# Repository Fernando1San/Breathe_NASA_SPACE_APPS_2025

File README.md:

# Breathe_NASA_SPACE_APPS_2025
2025 Hackathon for NASA all code and information
## Overview
Breathe is a mobile and IoT application developed in MIT App Inventor that enables real time monitoring and prediction of air quality, integrating information from Sentinel-5P TROPOMI satellite mission and low-cost environmental sensors.

The system collects, analyzes, and visualizes air pollution data to provide users with personalized health recommendations based on their environment and personal profile.

In addition to its mobile and IoT components, Breathe also includes an AI powered chatbot linked to ChatGPT, which allows users to interact naturally with the system,  asking questions about air quality, understanding pollutant levels, and receiving guidance on how to stay safe in varying atmospheric conditions.

Furthermore, the project features a dedicated web platform that shares educational resources, real-time updates, and information about the project’s technologies and environmental impact. This website aims to raise public awareness and promote community participation in air-quality monitoring.
The goal of Breathe is to protect public health, raise environmental awareness, and promote citizen participation in air quality measurement—combining satellite science, sensor technology, and artificial intelligence in a collaborative ecosystem.

## App Video 
https://youtube.com/shorts/2b4xFa8w2Ws?feature=share

## Download App
https://drive.google.com/file/d/1CBSrnyRV_KwNRinMbwZoVWh6irQ37grQ/view?usp=drivesdk

## Web Site
https://s0ma9dp.github.io/BREATHE/

## Repo Navigation suggestions
Throughout the folders, you’ll find README files that explain each section and its code.

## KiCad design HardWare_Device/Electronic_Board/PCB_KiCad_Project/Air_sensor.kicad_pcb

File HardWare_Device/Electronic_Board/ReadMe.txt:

#Electronic PCB
La PCB está basada en el microcontrolador ESP32-WROOM-32UE, un módulo con Wi-Fi y Bluetooth integrados, ideal para aplicaciones IoT que requieren comunicación inalámbrica estable y bajo consumo energético.
El circuito permite la conexión y lectura de diversos sensores de gases y partículas, ofreciendo una plataforma compacta y versátil para el monitoreo ambiental.

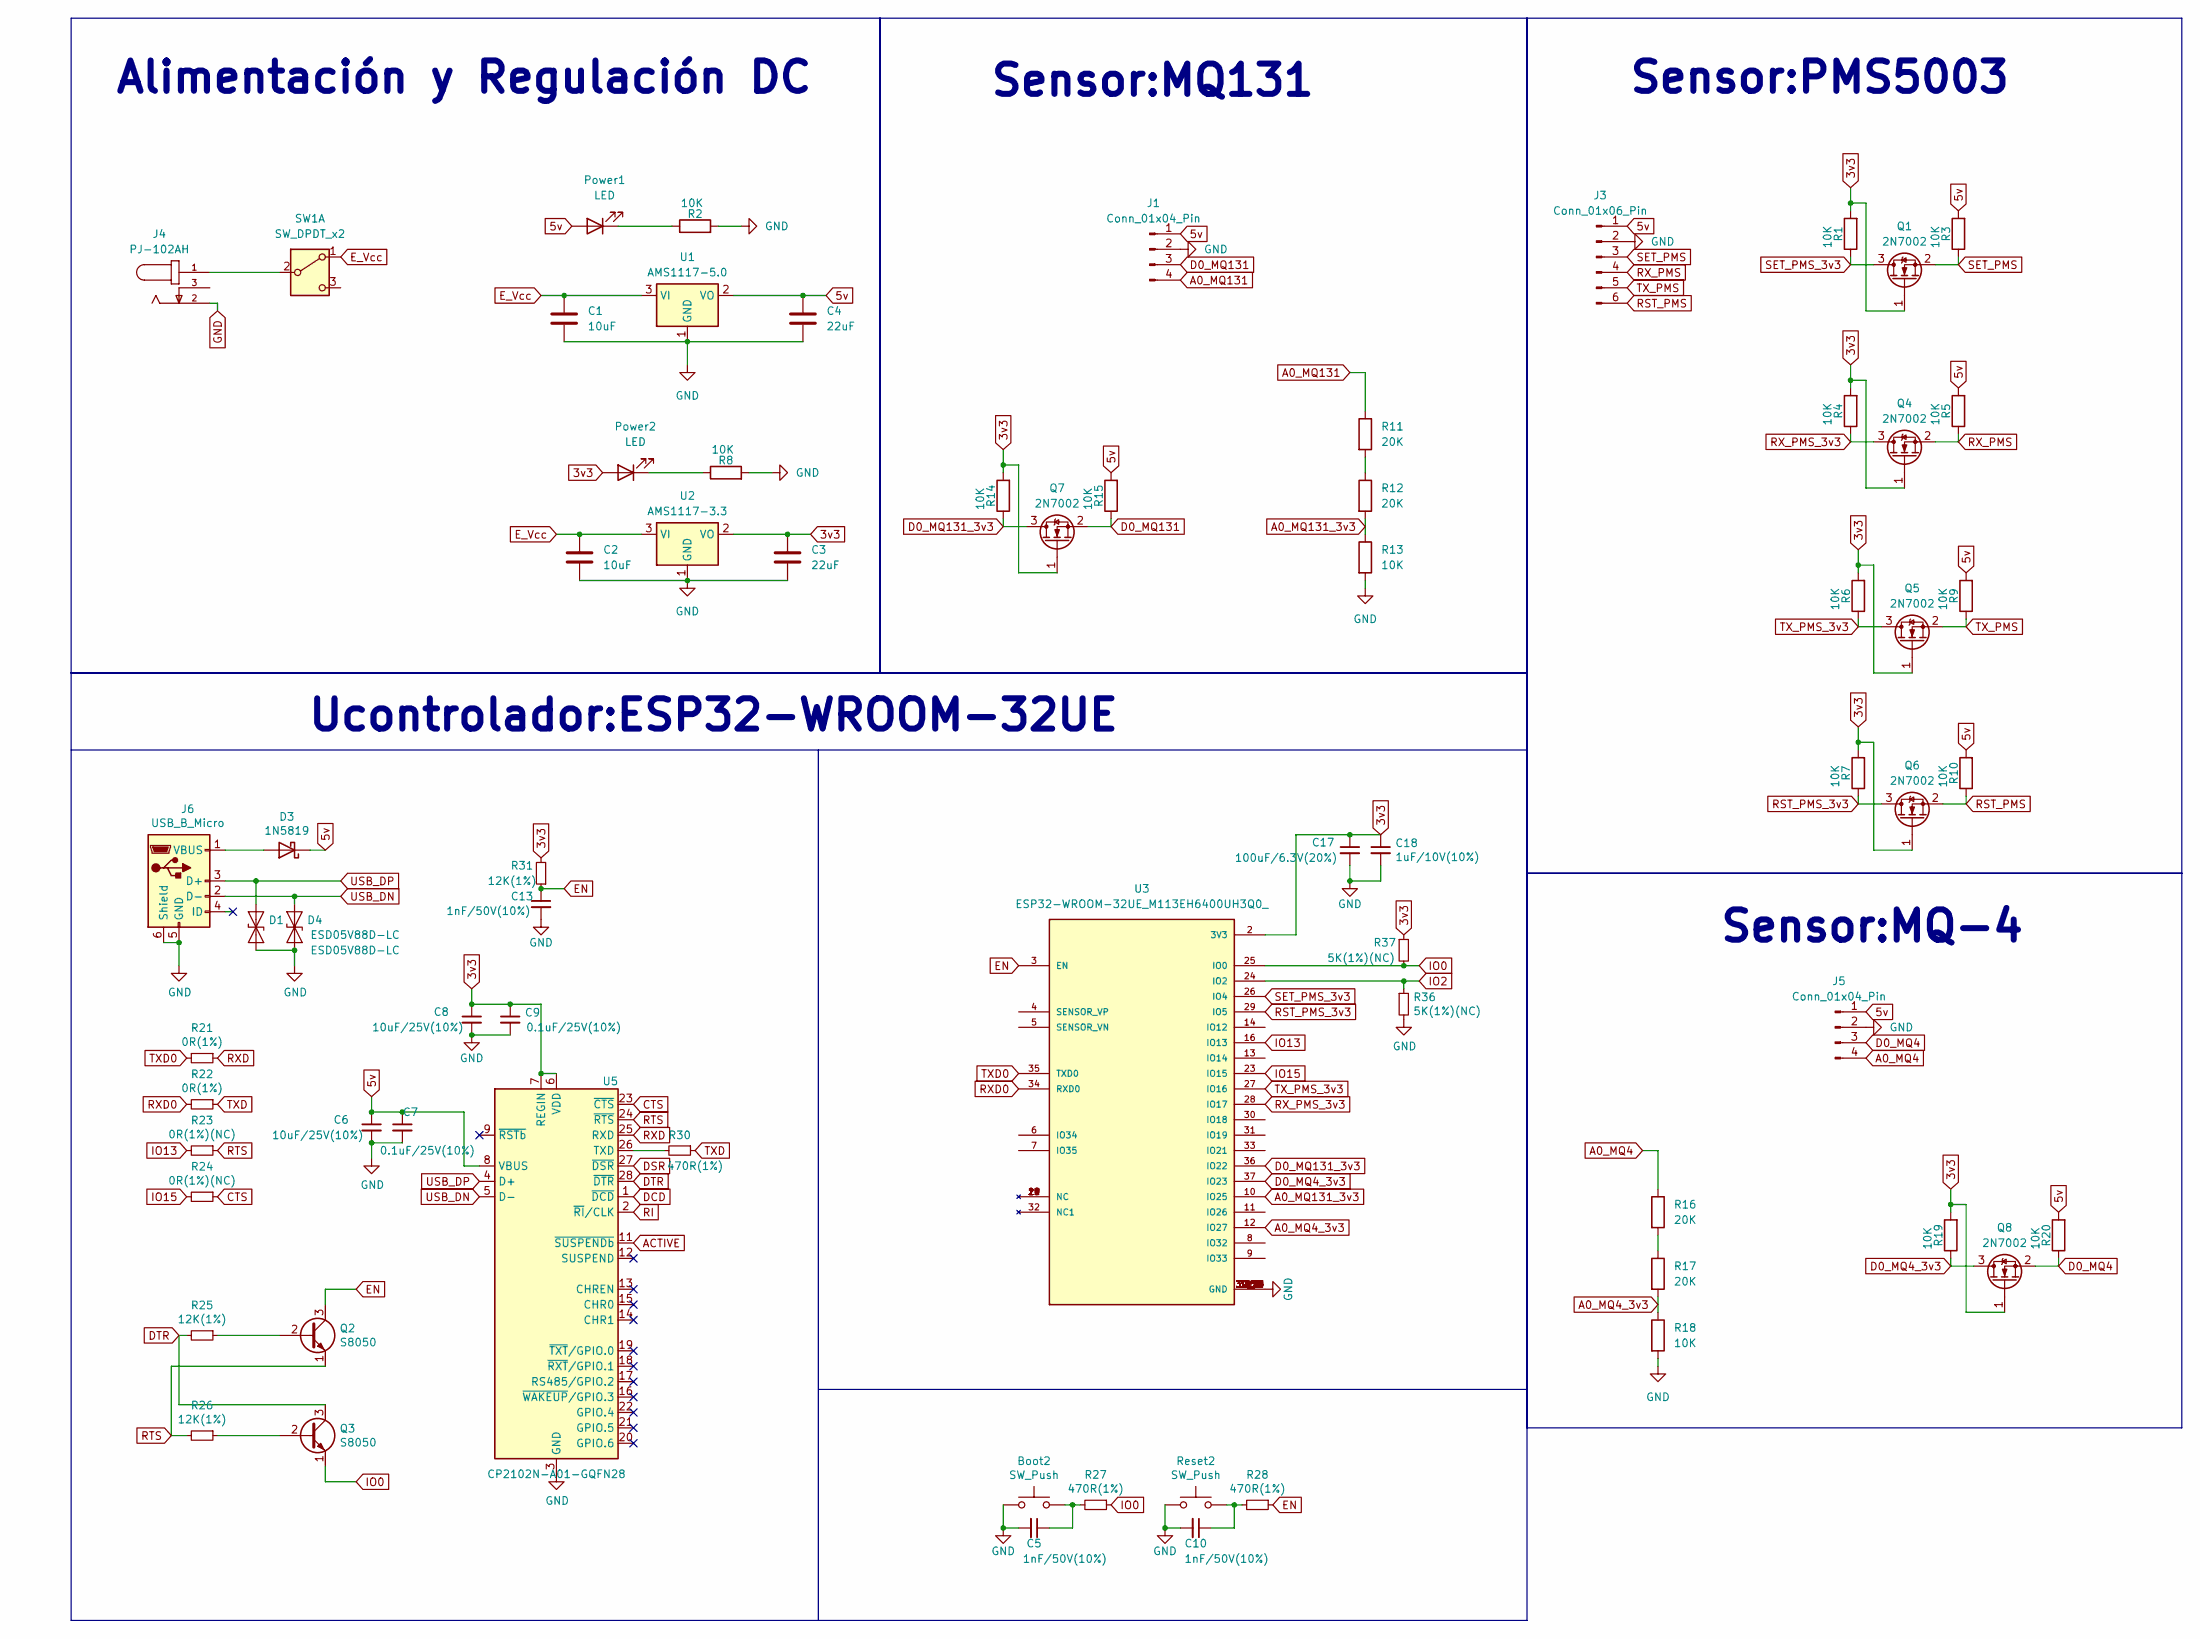
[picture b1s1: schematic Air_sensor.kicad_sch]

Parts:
Boot2: SW_Push; SW_Push_SPST_NO_Alps_SKRK
C1, C2: 10uF; CP_Radial_D4.0mm_P2.00mm
C3, C4: 22uF; CP_Radial_D4.0mm_P2.00mm
C5, C10, C13: 1nF/50V(10%); C_0402_1005Metric
C6, C8: 10uF/25V(10%); C_0603_1608Metric
C7, C9: 0.1uF/25V(10%); C_0402_1005Metric
C17: 100uF/6.3V(20%); C_0603_1608Metric
C18: 1uF/10V(10%); C_0402_1005Metric
D1, D4: ESD05V88D-LC; D_0402_1005Metric
D3: 1N5819; D_0402_1005Metric
J1, J5: Conn_01x04_Pin; PinHeader_1x04_P2.54mm_Horizontal
J3: Conn_01x06_Pin; PinHeader_1x06_P2.54mm_Horizontal
J4: PJ-102AH; CUI_PJ-102AH
J6: USB_B_Micro; USB_Micro-B_Molex_47346-0001
Power1, Power2: LED; LED_1206_3216Metric_Pad1.42x1.75mm_HandSolder
Q1, Q4, Q5, Q6, Q7, Q8: 2N7002; SOT-23
Q2, Q3: S8050; SOT-23
R1, R3, R4, R5, R6, R7, R9, R10, R14, R15, R19, R20: 10K; R_0402_1005Metric
R2, R8, R13, R18: 10K; R_1206_3216Metric_Pad1.30x1.75mm_HandSolder
R11, R12, R16, R17: 20K; R_1206_3216Metric_Pad1.30x1.75mm_HandSolder
R21, R22: 0R(1%); R_0402_1005Metric
R23, R24: 0R(1%)(NC); R_0402_1005Metric
R25, R26, R31: 12K(1%); R_0402_1005Metric
R27, R28: 470R(1%); R_0402_1005Metric
R30: 470R(1%); C_0402_1005Metric
R36, R37: 5K(1%)(NC); R_0402_1005Metric
Reset2: SW_Push; SW_Push_SPST_NO_Alps_SKRK
SW1: SW_DPDT_x2; SW_CK_JS202011AQN_DPDT_Angled
U1: AMS1117-5.0; SOT-223-3_TabPin2
U2: AMS1117-3.3; SOT-223-3_TabPin2
U3: ESP32-WROOM-32UE_M113EH6400UH3Q0_; MODULE_ESP32-WROOM-32UE_M113EH6400UH3Q0_; PARTREV 1.2
U5: CP2102N-A01-GQFN28; QFN-28-1EP_5x5mm_P0.5mm_EP3.35x3.35mm

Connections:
3v3: C3.1, C8.1, C9.1, C17.1, C18.1, Power2.2 (A), Q1.1 (G), Q4.1 (G), Q5.1 (G), Q6.1 (G), Q7.1 (G), Q8.1 (G), R1.2, R4.2, R6.2, R7.2, R14.2, R19.2, R31.2, R37.1, U2.2 (VO), U3.2 (3V3), U5.6 (VDD), U5.7 (REGIN)
5v: C4.1, C6.1, C7.1, D3.1 (K), J1.1, J3.1, J5.1, Power1.2 (A), R3.2, R5.2, R9.2, R10.2, R15.2, R20.2, U1.2 (VO), U5.8 (VBUS)
A0_MQ4: J5.4, R16.1
A0_MQ4_3v3: R17.2, R18.1, U3.12 (IO27)
A0_MQ131: J1.4, R11.1
A0_MQ131_3v3: R12.2, R13.1, U3.10 (IO25)
ACTIVE: U5.11 (~SUSPENDb)
CTS: R24.1, U5.23 (~CTS)
D0_MQ4: J5.3, Q8.2 (S), R20.1
D0_MQ4_3v3: Q8.3 (D), R19.1, U3.37 (IO23)
D0_MQ131: J1.3, Q7.2 (S), R15.1
D0_MQ131_3v3: Q7.3 (D), R14.1, U3.36 (IO22)
DCD: U5.1 (~DCD)
DSR: U5.27 (~DSR)
DTR: Q3.3 (C), R25.2, U5.28 (~DTR)
EN: C13.1, Q2.3 (C), R28.1, R31.1, U3.3 (EN)
E_Vcc: C1.1, C2.1, SW1.1 (A), U1.3 (VI), U2.3 (VI)
GND: Boot2.1, C1.2, C2.2, C3.2, C4.2, C5.2, C6.2, C7.2, C8.2, C9.2, C10.2, C13.2, C17.2, C18.2, D1.2 (A2), D4.2 (A2), J1.2, J3.2, J4.2, J5.2, J6.5 (GND), J6.6 (Shield), R2.2, R8.2, R13.2, R18.2, R36.2, Reset2.1, U1.1 (GND), U2.1 (GND), U3.1 (GND), U3.15 (GND), U3.38 (GND), U3.39_1 (GND), U3.39_2 (GND), U3.39_3 (GND), U3.39_4 (GND), U3.39_5 (GND), U3.39_6 (GND), U3.39_7 (GND), U3.39_8 (GND), U3.39_9 (GND), U3.39_10 (GND), U3.39_11 (GND), U3.39_12 (GND), U3.39_13 (GND), U3.39_14 (GND), U3.39_15 (GND), U3.39_16 (GND), U3.39_17 (GND), U3.39_18 (GND), U3.39_19 (GND), U3.39_20 (GND), U3.39_21 (GND), U5.3 (GND), U5.29 (GND)
IO0: Q3.1 (E), R27.1, R37.2, U3.25 (IO0)
IO2: R36.1, U3.24 (IO2)
IO13: R23.2, U3.16 (IO13)
IO15: R24.2, U3.23 (IO15)
unnamed: Boot2.2, C5.1, R27.2
unnamed: C10.1, R28.2, Reset2.2
unnamed: D3.2 (A), J6.1 (VBUS)
unnamed: Power1.1 (K), R2.1
unnamed: Power2.1 (K), R8.1
unnamed: Q2.2 (B), R25.1
unnamed: Q3.2 (B), R26.1
unnamed: R11.2, R12.1
unnamed: R16.2, R17.1
unnamed: J4.1, SW1.2 (B)
unnamed: R30.2, U5.26 (TXD)
RI: U5.2 (~RI/CLK)
RST_PMS: J3.6, Q6.2 (S), R10.1
RST_PMS_3v3: Q6.3 (D), R7.1, U3.29 (IO5)
RTS: Q2.1 (E), R23.1, R26.2, U5.24 (~RTS)
RXD: R21.1, U5.25 (RXD)
RXD0: R22.2, U3.34 (RXD0)
RX_PMS: J3.4, Q4.2 (S), R5.1
RX_PMS_3v3: Q4.3 (D), R4.1, U3.28 (IO17)
SET_PMS: J3.3, Q1.2 (S), R3.1
SET_PMS_3v3: Q1.3 (D), R1.1, U3.26 (IO4)
TXD: R22.1, R30.1
TXD0: R21.2, U3.35 (TXD0)
TX_PMS: J3.5, Q5.2 (S), R9.1
TX_PMS_3v3: Q5.3 (D), R6.1, U3.27 (IO16)
USB_DN: D4.1 (A1), J6.2 (D-), U5.5 (D-)
USB_DP: D1.1 (A1), J6.3 (D+), U5.4 (D+)

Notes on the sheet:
Sensor:MQ-4
Sensor:MQ131
Ucontrolador:ESP32-WROOM-32UE
Sensor:PMS5003
Alimentación y Regulación DC

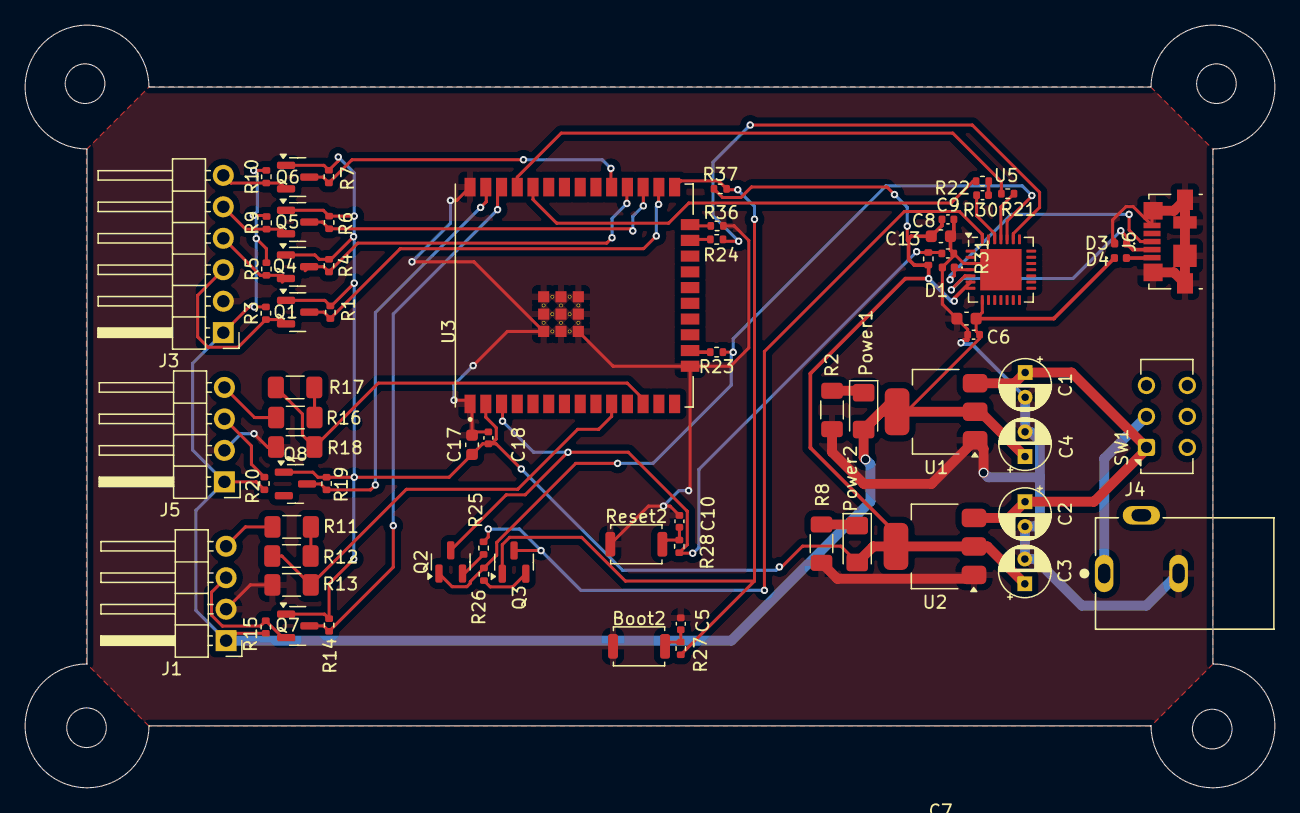
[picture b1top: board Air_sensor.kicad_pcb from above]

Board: 2 copper layers, 100.9 x 61.6 mm, 70 parts (0 on the bottom side), 45 nets.

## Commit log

2025-10-05 chore: ignore .env and sensitive environment files
2025-10-05 README.md
2025-10-05 breathe_API, test1 ready
2025-10-05 requirements for python added
2025-10-05 render deployment things
2025-10-05 render deployment
